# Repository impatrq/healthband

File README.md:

## ¿Qué es HealthBand? 💗

**HealthBand** propone un sistema de monitoreo de salud constante e inteligente :thermometer:. Utilizará un dispositivo *wearable* que censará diferentes parámetros de salud, como frecuencia cardíaca, oxigenación sanguínea, temperatura corporal y movimiento :heart:. El dispositivo será programado para detectar niveles de salud anormales y emitir alertas en formas de vibraciones.

La incorporación de un Bot de Telegram 💬 permitirá recibir alertas, consultar el estado de salud e información general.

Su funcionamiento se complementará al de una aplicación móvil :iphone:, la cuál le permitirá al usuario disponer de su estado de salud en cualquier momento, así como tener acceso a registros previos, descargarlos y compartirlos.

## Objetivos 📈

Buscamos diseñar un sistema capaz de monitorear los signos vitales de una persona de forma inteligente y de fácil interpretación para sus usuarios,  siendo capaz de activar un protocolo de emergencias cuando se presente una complicacion de salud y salvar vidas. 

## ¿Quienes somos?👨‍🎓

### Somos un grupo de Estudiantes del séptimo año de la **Escuela Técnica N°7- IMPA**, de la especialidad **Aviónica** ✈️.

# Integrantes 🫂

* ###  Acuña, Alvaro

* ###  Giulianetti Bruno

* ###  Gomez, Gonzalo

* ###  Pagano, Tobias 

* ###  Perlo, Mateo:

🎥 Nuestro Video Presentación : [HealthBand](https://www.youtube.com/watch?v=138KptZaLyc)

Seguinos en nuestras redes sociales 

Consultanos vía mail a 📧: (mailto:healthband.aid@gmail.com) 

# Distinciones 🏆

HealthBand ha participado de las Olimpíadas Nacionales de Informática, Electrónica y Telecomunicaciones **ONIET** :atom:, organizadas por la ***Universidad Blas Pascal*** en Córdoba. En su participación ha sido premiado con el ***Primer Puesto*** 🥇 en la competencia **Prototipos II** 🤖 y con un ***Tercer Puesto*** 🥉 en la competencia **FirstPlan** 🕴️

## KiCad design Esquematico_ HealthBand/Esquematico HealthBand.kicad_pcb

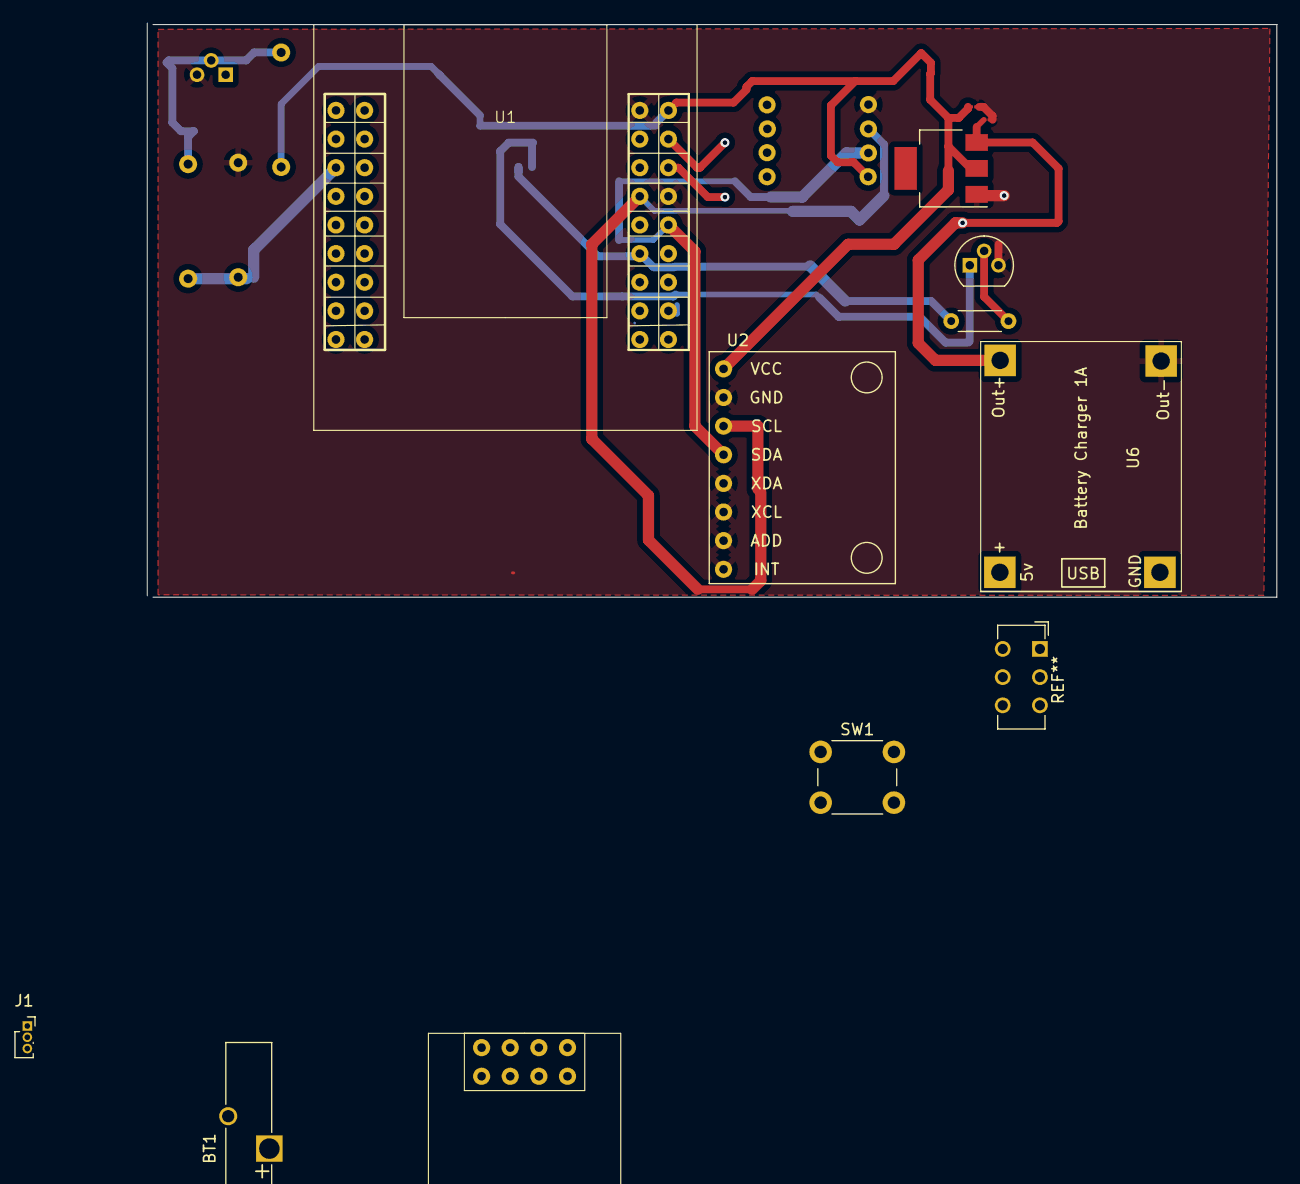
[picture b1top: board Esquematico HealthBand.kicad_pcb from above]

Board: 2 copper layers, 100.2 x 50.9 mm, 11 parts (1 on the bottom side), 7 nets.

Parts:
BT1: Battery; Battery_Panasonic_CR1632-V1AN_Vertical_CircularHoles
C1: C; C_01005_0402Metric
C2: C; C_01005_0402Metric_Pad0.57x0.30mm_HandSolder
J1: Conn_01x03_Socket; PinSocket_1x03_P1.00mm_Vertical
M1: Motor_DC; MOTOR_DC
SW1: SW_DIP_x01; SW_PUSH_6mm_H5mm
U1: ESP32-WROOM-32U; ESP32_BOARD
U2: MPU-6050; module_mpu6050
U4-USB_TO_UART_CH340G1: USB_TO_UART_CH340G
U5: LM1117DT-3.3; SOT-223
U6: TP4056; TP4056-18650

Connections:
GNDREF: BT1.2 (-), C1.1, C2.2, J1.3, U1.GND, U2.2 (VDD), U2.5 (CLKIN), U2.6 (AUX_DA), U2.7 (AUX_CL), U2.8 (INT), U5.1 (GND), U6.4 (OUT-)
IO15: M1.1 (-), U1.IO15
unnamed: BT1.1 (+), SW1.1
unnamed: C1.2, SW1.2, U5.3 (VI), U6.3 (OUT+)
SCL: U1.IO22, U2.3 (VLOGIC)
SDA: U1.IO21, U2.4 (AD0)
VDD: C2.1, U1.3v3, U2.1 (GND), U5.2 (VO)

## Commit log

2023-04-28 feat: agregar mensaje de hola mundo
2023-04-28 fix: actualizar tipo de retorno
2023-04-28 chore: ignorar ejecutable main
2023-05-05 Docs: Agregar Quienes somos, Objetivo, Foto Grupal y Contactos
2023-05-05 Docs: Agregar Objetivos, Foto grupal, y contactos.
2023-05-05 Agregar foto grupal y contactos
    agregue los objetivos
2023-05-05 docs: agregar foto grupal y estilos varios
2023-05-05 docs: agregar foto y estilos varios
2023-07-04 Proyecto React Native
2023-10-10 Deleted files
    Se borran archivos que se clonaron accidentalmente
2023-10-10 Django and WebApp
    se agrega Django, y se traslada la web a los template para que django los renderice y ejecute
2023-10-11 Test Web
    Se suve una version preliminar de la pagina para poder intentar hostearla en vercell.
2023-10-11 vercel requirements
    se suben cosas necesarias para subir la pagina web a vercel.
2023-10-11 vercel
    se actuallizan los datos para que funcione la web en vercel
2023-10-11 host
    se activa el host en vercel
2023-10-11 app
    se declara app = application
2023-10-12 A
    A
2023-10-12 try
    intento de subir pagina a vercel
2023-10-12 test
2023-10-12 psycopg2 removed
2023-10-12 HOLAAA
2023-10-12 test 2
2023-10-12 DEBUG FALSE
2023-10-12 test
    test
2023-10-12 porfafunca
    por favor te pido que funciones codigo te lo ruego
2023-10-12 LAST DANCE
    LAST DANCE
2023-10-12 STATIC ROOT REMOVED
2023-10-12 static route change
2023-10-12 vercel json refreshing
2023-10-14 test
    test style css
    and scipt js
2023-10-14 test
    test JS
2023-10-14 test
    test sin js
2023-10-15 test
    test recepcion de datos en la web
2023-10-15 test
    test again de mediciion de datos
2023-10-15 test
    test with cflsfns xcongir except
2023-10-16 test super test
    test funcional
2023-10-17 actualizacion gitignore
2023-10-17 update
    se agrega el dominio de www.healthband.com.ar a vercel
2023-10-20 construccion de appbar home y pantalla opening, se agregaron archivos de imagen
2023-10-20 creacion de bloques del cuerpo de la pantalla del home
2023-10-20 4 bloques + bienvenida y boton descarga
2023-10-20 TEST
    se envia la pagina completamente actualizada para que pueda recibir y leer posts
2023-10-21 post
    pagina que muestra los datos
2023-10-21 sensor de temperatura corporal lm335 + motor de vibracion
2023-10-23 creacion de 4 widgets para la visualizacion de datos en home
2023-10-23 pequeños resizings de widgets + efecto scroll
2023-10-23 codigo + librerias mpu6050 (falta obtener datos de tiempo))
2023-10-24 creacion de archivo dart para interfaz de formulario de registro
2023-10-24 enviroment context variables for db
2023-10-24 requirements
2023-10-24 asd
    asd
2023-10-24 host
    allowed host to www.healthband.com.ar
2023-10-24 xd
    xd
2023-10-25 commit
    se suben el codigo completo de todos los archivos
2023-10-26 pruebas infrarrojas
2023-10-30 pruebas para formulario pdf home
2023-10-30 creacion pantalla perfil + agregar foto de perfil
2023-11-03 form validado + intento get http response para muestra de datos home
2023-11-03 agregado status code para chequeos de comunicacion en la transmision de datos
2023-11-03 agregado de funcion para metodos get
2023-11-03 creacion de archivo .env y agregado de claves para el hosteo
2023-11-07 muestreo de datos en la app, falta darle estilos a la screen
2023-11-10 prueba de pwm con led ir - estabilizacion de los valores de o2
2023-11-11 implementación de conversor a pdf - investigacion y configuracion de funciones para notificaciones
2023-11-12 nuevos logos hb para iconos
2023-11-12 new icons + funcion de boton emergencias
2023-11-12 Documentación del proyecto
2023-11-14 refresh manual y automatico + estilos a bloques segun datos
2023-11-14 ninikjnjlnhkbgvyfctdxreydctufvybgmj,kl
    mauricio macri
2023-11-14 Bot
    Se sube el bot de telegram completo y funcional a github
2023-11-14 readme
    se sube el readme a main
2023-11-14 Codes Update
    Se suben los codigos completos de los sensores, a su vez, el codigo principal funcional
2023-11-14 Git fix
    se elimina carpeta de pagina web mal clonada
2023-11-14 Git fix
    se elimina mala clonacion de carpeta pagina web
2023-11-14 BBDD update
2023-11-15 form de registro de usuario + pantalla profile
2023-11-15 estilos bottom navbar actualizados
2023-11-15 Modelado 3D
2023-11-15 Esquematico HB
2023-11-15 Anteproyecto + Historias de Usuario
2023-11-15 Backlog
2023-11-16 historial en tiempo de mediciones
2023-11-16 planos acotados de las partes de la carcasa
2023-11-17 creacion de boton de historial pdf
2023-11-18 assets
2023-11-18 foto grupal
2023-11-18 agregado foto grupal readme
2023-11-18 dispositivo
2023-11-18 pulsera
2023-11-18 foto app
2023-11-18 certificados jpg e icono mail
2023-11-20 agregar geolocalización
2023-11-20 fotos jpg
2023-11-20 imagenes jpg
2023-11-20 geolocalización implementada
2023-11-22 asd
    aasd
2023-11-22 presentación para exposición en entrepiso
2023-11-23 arreglo
2023-11-23 Representación grafica de prueba de la red neuronal
2023-11-23 Datos de usuarios
2023-11-23 Nivel de glucosa en diferentes usuarios
2023-11-23 Funcionamiento del led infrarrojo
2023-11-23 Guía de funcionamiento de MATLAB
2023-11-23 Etapa de entrenamiento de la red neuronal
2023-11-23 Perfromance
2023-11-23 diagrama
    esp32 a sensor de pulso y oxígeno MAX30102
2023-11-23 Estado visual de entrenamiento
2023-11-23 Grafico visual de margen de error
2023-11-23 esp32
    diagrama de pines
2023-11-23 Grafico visual de las validaciones
2023-11-23 lm335
    diagrama
2023-11-23 18B20
    conexión a esp32
2023-11-23 motor vibrador
    ...
2023-11-23 MPU6050
    conexión a micro
2023-11-23 facturas de compra
2023-11-23 Red Neuronal de HealthBand
2023-11-23 Create Documento con ordenes de Compra - Proyecto HealthBand - 7mo 1ra Avionica Comision A.pdf
    ...
2023-11-24 parte abajo final
    ...
2023-11-24 parte arriba final
    ...
2023-11-24 Primer esquemático parte superior
2023-11-24 Primer esquemático parte inferior
2023-11-24 primera placa
    ...
2023-11-24 primera placa b
    ...
2023-11-24 Create segunda placa echa.jpeg
    ...
2023-11-24 Create segunda placa echa b.jpeg
    ...
2023-11-24 Create tercera placa .jpeg
    ...
2023-11-24 Create tercera placa b.jpeg
    ...
2023-11-24 Create anteultima placa.jpeg
    ...
2023-11-24 Create anteultima placa b.jpeg
    ...
2023-11-24 Create peor placa echa.jpeg
    ....
2023-11-24 Create README.md
    explicación
2023-11-24 Rename Datos de la Red Neuronal.xlsx to Datos usados de la Red Neuronal.xlsx
2023-11-24 Rename Entrenamiento.png to Etapa de entrenamiento.png
2023-11-24 Rename Glucosa.xlsx to Excel con los datos de glucosa.xlsx
2023-11-24 Rename Performance.png to Estado de actividad.png
2023-11-24 Rename Led Infrarrojo.docx to informacion del led Infrarrojo.docx
2023-11-25 Carcasa (arriiba)
    vista de arriba HB
2023-11-25 Carcasa (de frente)
    vista de frente HB (1ra version)
2023-11-25 Carcasa (de lado)
    vista de lado HB (1ra version)
2023-11-25 Carcasa (lado trasero)
    vista lado trasero HB (1ra version)
2023-11-25 Carcasa (abajo)
    vista de abajo HB (1ra version)
2023-11-25 Carcasa (isometrica)
    vista isometrica HB (1ra version)
2023-11-25 Carcasa (completa)
    vista isometrica abierta HB (1ra version)
2023-11-25 PCB vista inferior
    modelo 3D PCB
2023-11-25 creacion de carpeta
    se hizo una carpeta para los modelos 3D del PCB
2023-11-25 PCB vista de arriba
    modelo 3D PCB
2023-11-25 PCB vista isometrica de abajo
    modelo 3D PCB
2023-11-25 PCB vista isometrica de arriba
    modelo 3D PCB
2023-11-25 planos HB version beta
    plano con las vistas del primer diseño (boceto)
2023-11-25 bocetos HB 1
    .
2023-11-25 bocetos HB 2
2023-11-25 bocetos HB 3
2023-11-25 bocetos HB 4
2023-11-25 paso a carpeta "bocetos"
2023-11-25 HealthBand beta
    primera estructura diseñada
2023-11-25 Bocetos de logo
2023-11-25 Logo final HB
